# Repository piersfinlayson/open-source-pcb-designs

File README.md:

# open-source-pcb-designs

All PCB designs in this github repository are made available under the [GPLv3](https://www.gnu.org/licenses/gpl-3.0.en.html) license.

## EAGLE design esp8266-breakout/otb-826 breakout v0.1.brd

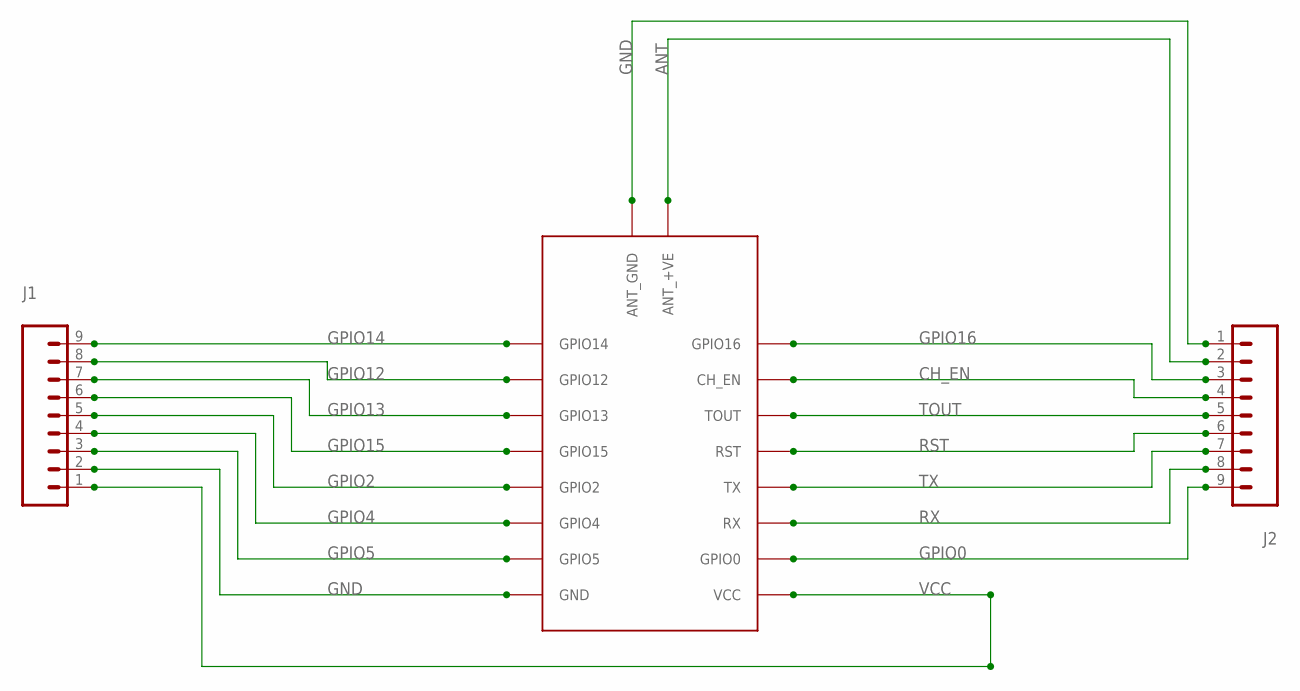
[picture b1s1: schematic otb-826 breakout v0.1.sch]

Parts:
J1, J2: M09; 1X09
OTB-8266: OTB-8266-V0.1

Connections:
ANT: J2.2, OTB-8266.ANT_+VE
CH_EN: J2.4, OTB-8266.CH_EN
GND: J1.2, J2.1, OTB-8266.ANT_GND, OTB-8266.GND
GPIO0: J2.9, OTB-8266.GPIO0
GPIO2: J1.5, OTB-8266.GPIO2
GPIO4: J1.4, OTB-8266.GPIO4
GPIO5: J1.3, OTB-8266.GPIO5
GPIO12: J1.8, OTB-8266.GPIO12
GPIO13: J1.7, OTB-8266.GPIO13
GPIO14: J1.9, OTB-8266.GPIO14
GPIO15: J1.6, OTB-8266.GPIO15
GPIO16: J2.3, OTB-8266.GPIO16
RST: J2.6, OTB-8266.RST
RX: J2.8, OTB-8266.RX
TOUT: J2.5, OTB-8266.TOUT
TX: J2.7, OTB-8266.TX
VCC: J1.1, OTB-8266.VCC

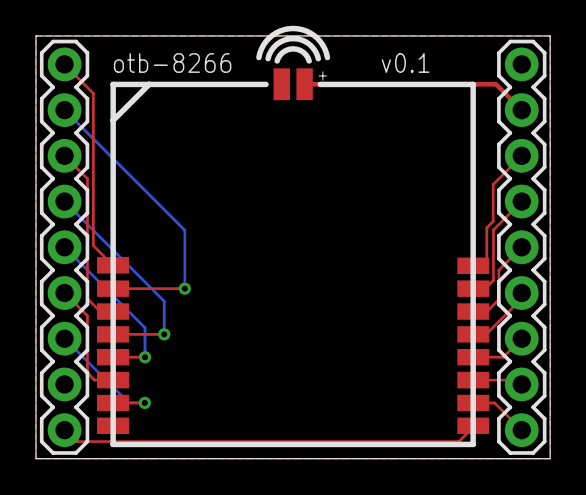
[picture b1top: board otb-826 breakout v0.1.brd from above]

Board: 2 copper layers, 28.6 x 23.5 mm, 3 parts (0 on the bottom side), 17 nets.

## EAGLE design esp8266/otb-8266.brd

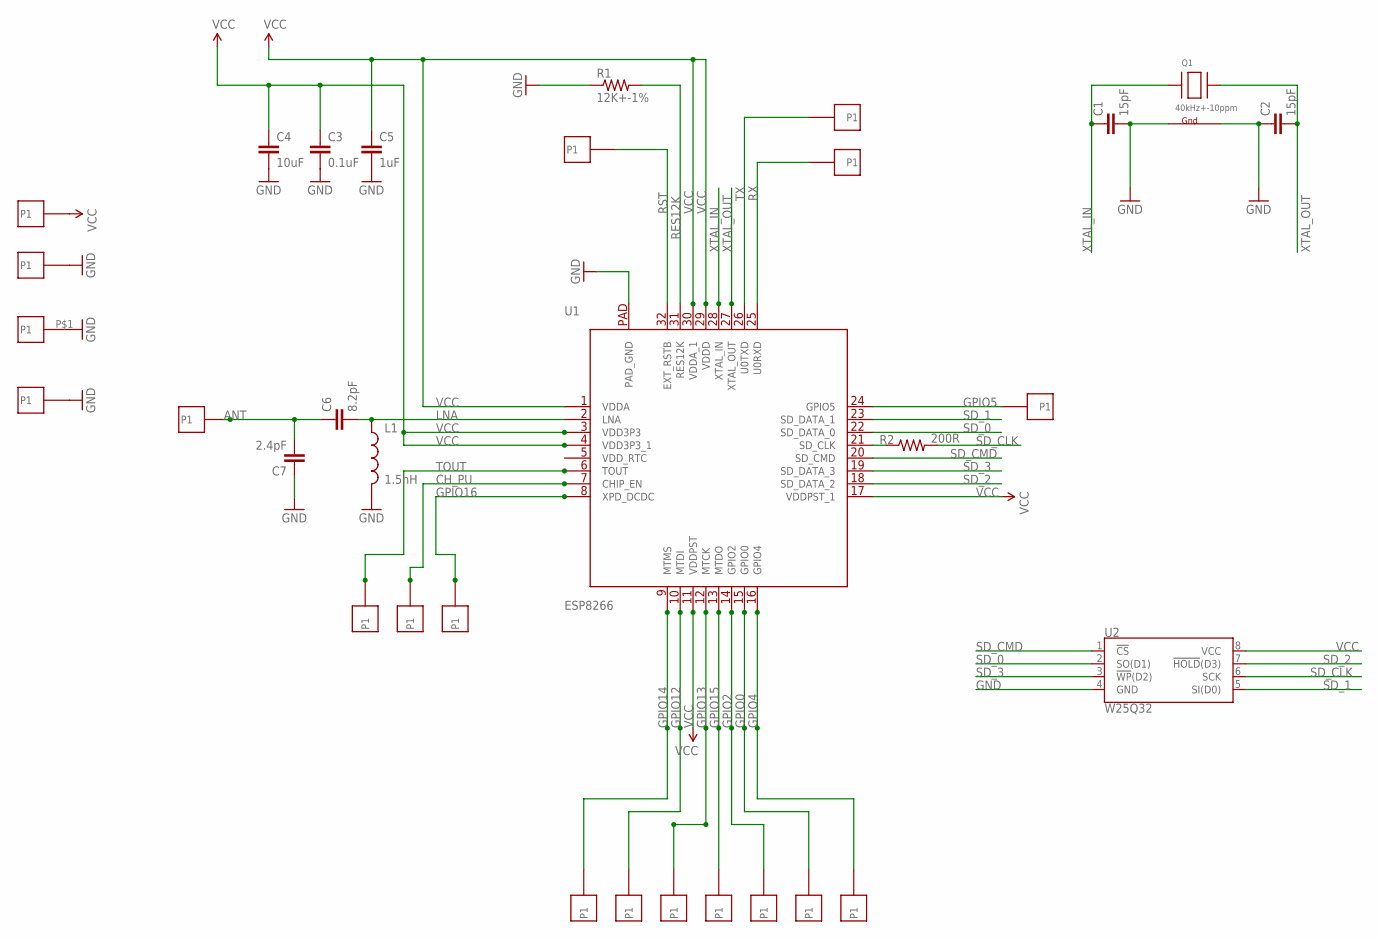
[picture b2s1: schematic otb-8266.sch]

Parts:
C1, C2: 15pF; 0402-CAP
C3: 0.1uF; 0402-CAP
C4: 10uF; 0603-CAP
C5: 1uF; 0603-CAP
C6: 8.2pF; 0402-CAP
C7: 2.4pF; 0402-CAP
L1: 1.5nH; C0402
Q1: 40kHz+-10ppm; NX3225
R1: 12K+-1%; 0402-RES
R2: 200R; 0402-RES
U1: ESP8266; QFN32
U2: W25Q32; SOIC-8
U$1, U$2, U$3, U$4, U$5, U$6, U$7, U$8, U$9, U$10, U$11, U$12, U$13, U$14, U$15, U$16, U$18, U$19: 1.27MM_PITCH_PLATED_HOLE
U$17: 17X18MM_PCB_SHIELD; 17X18_SHIELD

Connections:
ANT: C6.1, C7.2, U$16.P1
CH_PU: U1.7 (CHIP_EN), U$4.P1
GND: C1.2, C2.1, C3.2, C4.2, C5.2, C7.1, L1.2, Q1.2 (G2), Q1.4 (G1), R1.1, U1.EP (PAD_GND), U2.4 (GND), U$2.P1, U$17.P$1, U$19.P1
GPIO0: U1.15 (GPIO0), U$11.P1
GPIO2: U1.14 (GPIO2), U$10.P1
GPIO4: U1.16 (GPIO4), U$12.P1
GPIO5: U1.24 (GPIO5), U$18.P1
GPIO12: U1.10 (MTDI), U$7.P1
GPIO13: U1.12 (MTCK), U$8.P1
GPIO14: U1.9 (MTMS), U$6.P1
GPIO15: U1.13 (MTDO), U$9.P1
GPIO16: U1.8 (XPD_DCDC), U$5.P1
LNA: C6.2, L1.1, U1.2 (LNA)
unnamed: R2.1, U1.21 (SD_CLK)
RES12K: R1.2, U1.31 (RES12K)
RST: U1.32 (EXT_RSTB), U$15.P1
RX: U1.25 (U0RXD), U$13.P1
SD_0: U1.22 (SD_DATA_0), U2.2 (SO(D1))
SD_1: U1.23 (SD_DATA_1), U2.5 (SI(D0))
SD_2: U1.18 (SD_DATA_2), U2.7 (!HOLD!(D3))
SD_3: U1.19 (SD_DATA_3), U2.3 (!WP!(D2))
SD_CLK: R2.2, U2.6 (SCK)
SD_CMD: U1.20 (SD_CMD), U2.1 (!CS!)
TOUT: U1.6 (TOUT), U$3.P1
TX: U1.26 (U0TXD), U$14.P1
VCC: C3.1, C4.1, C5.1, U1.1 (VDDA), U1.3 (VDD3P3), U1.4 (VDD3P3_1), U1.11 (VDDPST), U1.17 (VDDPST_1), U1.29 (VDDD), U1.30 (VDDA_1), U2.8 (VCC), U$1.P1
XTAL_IN: C1.1, Q1.1 (X1), U1.28 (XTAL_IN)
XTAL_OUT: C2.2, Q1.3 (X2), U1.27 (XTAL_OUT)

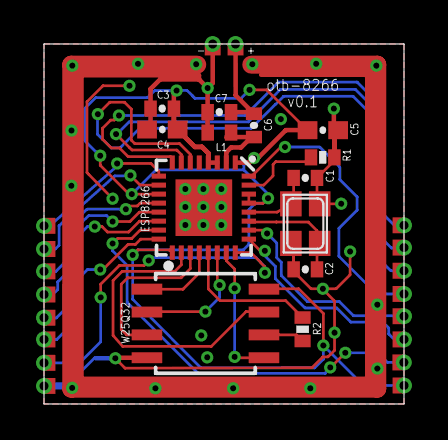
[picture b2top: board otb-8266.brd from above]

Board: 2 copper layers, 20.0 x 20.0 mm, 32 parts (0 on the bottom side), 28 nets.

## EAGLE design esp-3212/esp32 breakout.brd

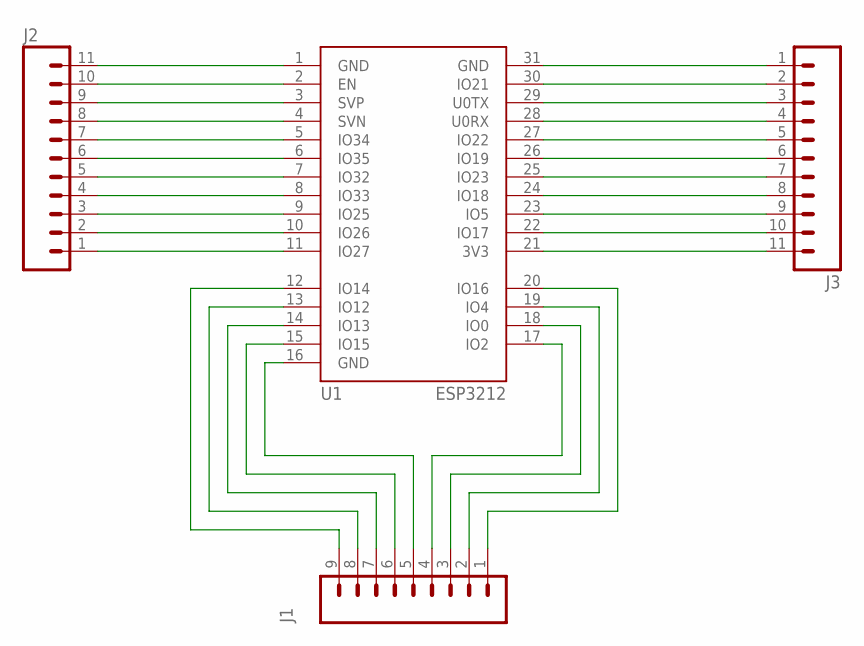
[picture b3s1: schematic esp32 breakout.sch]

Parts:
J1: M09; 1X09
J2, J3: M11PTH; 1X11
U1: ESP3212

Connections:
unnamed: J2.11, U1.1 (GND)
unnamed: J2.10, U1.2 (EN)
unnamed: J2.9, U1.3 (SVP)
unnamed: J2.8, U1.4 (SVN)
unnamed: J2.7, U1.5 (IO34)
unnamed: J2.6, U1.6 (IO35)
unnamed: J2.5, U1.7 (IO32)
unnamed: J2.4, U1.8 (IO33)
unnamed: J2.3, U1.9 (IO25)
unnamed: J2.2, U1.10 (IO26)
unnamed: J2.1, U1.11 (IO27)
unnamed: J1.9, U1.12 (IO14)
unnamed: J1.8, U1.13 (IO12)
unnamed: J1.7, U1.14 (IO13)
unnamed: J1.6, U1.15 (IO15)
unnamed: J1.5, U1.16 (GND)
unnamed: J1.4, U1.17 (IO2)
unnamed: J1.3, U1.18 (IO0)
unnamed: J1.2, U1.19 (IO4)
unnamed: J1.1, U1.20 (IO16)
unnamed: J3.1, U1.31 (GND)
unnamed: J3.2, U1.30 (IO21)
unnamed: J3.3, U1.29 (U0TX)
unnamed: J3.4, U1.28 (U0RX)
unnamed: J3.5, U1.27 (IO22)
unnamed: J3.6, U1.26 (IO19)
unnamed: J3.7, U1.25 (IO23)
unnamed: J3.8, U1.24 (IO18)
unnamed: J3.9, U1.23 (IO5)
unnamed: J3.10, U1.22 (IO17)
unnamed: J3.11, U1.21 (3V3)

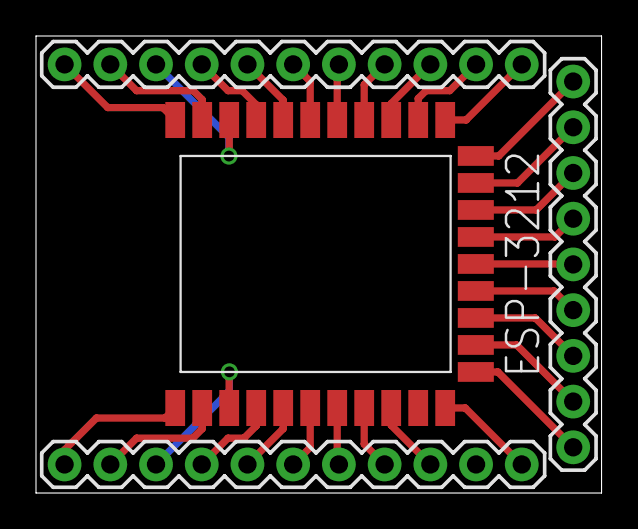
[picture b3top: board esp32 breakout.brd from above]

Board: 2 copper layers, 31.4 x 25.4 mm, 4 parts (0 on the bottom side), 31 nets.

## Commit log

2016-09-08 esp-3212 initial commit
2016-09-08 add attribution to MacroYau
2018-03-29 add esp8266 design
2018-03-29 add esp8266-breakout

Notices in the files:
parts and their libraries:
SparkFun-Connectors: Licensing: Creative Commons ShareAlike 4.0 International - https://creativecommons.org/licenses/by-sa/4.0
esp32: Creative Commons Attribution-ShareAlike 4.0 International
